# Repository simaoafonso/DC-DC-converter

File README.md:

# DC-DC-converter
CONVERSOR DC-DC ISOLADO PARA ENERGY ROUTER

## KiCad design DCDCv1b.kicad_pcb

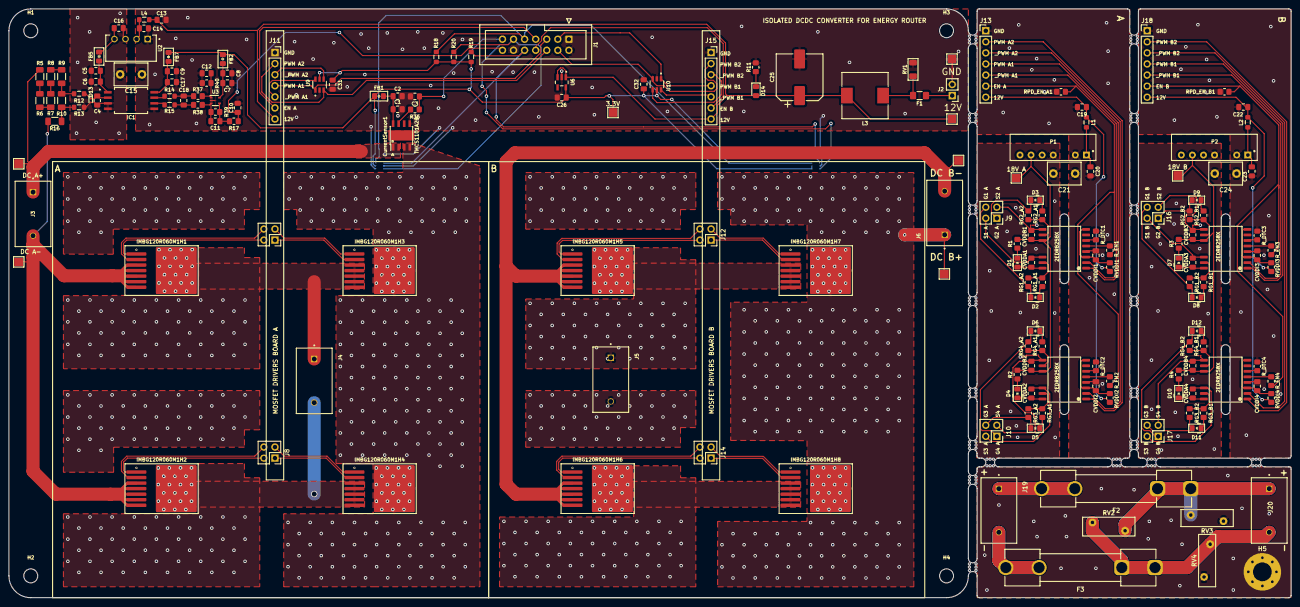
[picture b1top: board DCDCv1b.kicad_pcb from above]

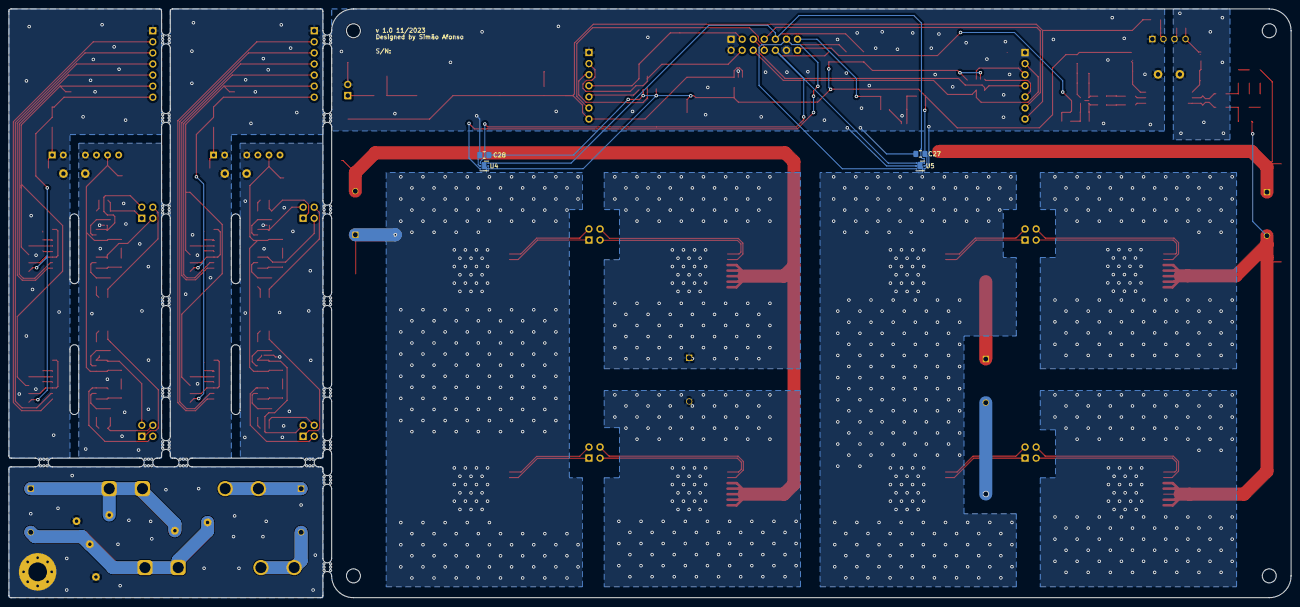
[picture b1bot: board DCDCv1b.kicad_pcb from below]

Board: 2 copper layers, 294.0 x 135.0 mm, 205 parts (4 on the bottom side), 112 nets.

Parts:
2EDR8258X1, 2EDR8258X2, 2EDR8258X3, 2EDR8258X4: U; 2EDR8258X
3.3V, 18V A, 18V B: TestPoint; TestPoint_Pad_2.0x2.0mm
C1, C7, C17: 4.7u; C_0805_2012Metric_Pad1.18x1.45mm_HandSolder
C2, C3, C6, C8, C9, C10, C18, C27, C28, C31, C32: 0.1u; C_0805_2012Metric_Pad1.18x1.45mm_HandSolder
C4: 0.01u; C_0805_2012Metric_Pad1.18x1.45mm_HandSolder
C5: 1u; C_0805_2012Metric_Pad1.18x1.45mm_HandSolder
C11, C12: 680p; C_0805_2012Metric_Pad1.18x1.45mm_HandSolder
C13, C14: 4.7u 50v; C_0805_2012Metric_Pad1.18x1.45mm_HandSolder
C15: 270p 2kV; C_Disc_D7.5mm_W5.0mm_P5.00mm
C16: 10u 16v; C_0805_2012Metric_Pad1.18x1.45mm_HandSolder
C19, C20, C22, C23: 2.2u 100v; C_0805_2012Metric_Pad1.18x1.45mm_HandSolder
C21, C24: 470p 2kV; C_Disc_D7.5mm_W5.0mm_P5.00mm
C25: 680u 25V; CP_Elec_10x14.3
C26: 2.2u; C_0805_2012Metric_Pad1.18x1.45mm_HandSolder
CVDDA1, CVDDA2, CVDDA3, CVDDA4: 0.1uF; C_0805_2012Metric_Pad1.18x1.45mm_HandSolder
CVDDB1, CVDDB2, CVDDB3, CVDDB4: 0.1uF; C_0805_2012Metric_Pad1.18x1.45mm_HandSolder
CVDDI1, CVDDI2, CVDDI3, CVDDI4: 10n; C_0805_2012Metric_Pad1.18x1.45mm_HandSolder
CurrentSensor1: TMCS1101A2B; SOIC-8-1EP_3.9x4.9mm_Pitch1.27mm_HandSolder
D1, D2, D3, D4, D5, D6, D7, D8, D9, D10, D11, D12: D; D_0805_2012Metric_Pad1.15x1.40mm_HandSolder
D13: ESD5B5.0ST1G; D_SOD-923
D14: LED; LED_0805_2012Metric_Pad1.15x1.40mm_HandSolder
DC A-: TestPoint; TestPoint_Pad_2.0x2.0mm
DC B-: TestPoint; TestPoint_Pad_2.0x2.0mm
F1: 1A; Fuse_1206_3216Metric_Pad1.42x1.75mm_HandSolder
F2, F3: Fuse; Fuseholder_Clip-6.3x32mm_Littelfuse_102_Inline_P34.21x7.62m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
FB1, FB2, FB5, FB7: MH2029-300Y; Ferrite_0805_2012Metric_Pad1.15x1.40mm_BigPads
H1, H2, H3, H4: MountingHole; MountingHole_3.2mm_M3
H5: MountingHole_Pad; MountingHole_4.3mm_M4_Pad_Via
IC1: AMC1311DWVR; SOIC127P1150X280-8N
IMBG120R060M1H1, IMBG120R060M1H2, IMBG120R060M1H3, IMBG120R060M1H4, IMBG120R060M1H5, IMBG120R060M1H6, IMBG120R060M1H7, IMBG120R060M1H8: TO-263-7_TabPin8
J1: Conn_02x07_Odd_Even; IDC-Header_2x07_P2.54mm_Vertical
J2: Conn_01x02_Pin; PinHeader_1x02_P2.54mm_Vertical
J3, J4, J5, J6, J19, J20: 282838-2; TE_282838-2
J7, J8, J12, J14: Conn_02x02_Counter_Clockwise; PinSocket_2x02_P2.54mm_Vertical
J9, J10, J16, J17: Conn_02x02_Counter_Clockwise; PinHeader_2x02_P2.54mm_Vertical
J11, J15: Conn_01x07_Socket; PinSocket_1x07_P2.54mm_Vertical
J13, J18: Conn_01x07_Pin; PinHeader_1x07_P2.54mm_Vertical
L1, L2: 18u; L_0805_2012Metric_Pad1.05x1.20mm_HandSolder
L3: 82u; L_10.4x10.4_H4.8
L4: 6.8u; L_0805_2012Metric_Pad1.05x1.20mm_HandSolder
NT1, NT2, NT3, NT4: NetTie_2; R_01005_0402Metric
P1, P2: AM2D-1218SZ; AM2D-NZ
R1, R2, R3, R4: 2.4; R_0805_2012Metric_Pad1.20x1.40mm_HandSolder
R5, R6, R7, R8, R9: 402k 250mW; R_1206_3216Metric_Pad1.30x1.75mm_HandSolder
R10: 4K53 250mW; R_1206_3216Metric_Pad1.30x1.75mm_HandSolder
R11: 510; R_0805_2012Metric_Pad1.20x1.40mm_HandSolder
R12, R13: 39; L_0805_2012Metric_Pad1.05x1.20mm_HandSolder
R14, R15: 1k; L_0805_2012Metric_Pad1.05x1.20mm_HandSolder
R16: 0.001 1W; R_1206_3216Metric_Pad1.30x1.75mm_HandSolder
R17, R36: 68.1; R_0805_2012Metric_Pad1.20x1.40mm_HandSolder
R18, R19, R20: 5k; L_0805_2012Metric_Pad1.05x1.20mm_HandSolder
R37, R38: 1k; R_0805_2012Metric_Pad1.20x1.40mm_HandSolder
R39, R40: 3k2; R_0805_2012Metric_Pad1.20x1.40mm_HandSolder
RG1_A1, RG1_A2, RG1_B1, RG1_B2, RG2_A1, RG2_A2, RG2_B1, RG2_B2, RG3_A1, RG3_A2, RG3_B1, RG3_B2, RG4_A1, RG4_A2, RG4_B1, RG4_B2: 2.4; R_0805_2012Metric_Pad1.20x1.40mm_HandSolder
RPD_EN_A1: 10k; R_0805_2012Metric_Pad1.20x1.40mm_HandSolder
RPD_EN_B1: 10k; R_0805_2012Metric_Pad1.20x1.40mm_HandSolder
RV1: 14V; R_1206_3216Metric_Pad1.30x1.75mm_HandSolder
RV2: Varistor; RV_Disc_D12mm_W4.3mm_P7.5mm
RV3, RV4: Varistor; RV_Disc_D12mm_W3.9mm_P7.5mm
RVDDI1, RVDDI2, RVDDI3, RVDDI4: 3k; R_0805_2012Metric_Pad1.20x1.40mm_HandSolder
R_DTC1, R_DTC2, R_DTC3, R_DTC4: 10k; R_0805_2012Metric_Pad1.20x1.40mm_HandSolder
R_EN1, R_EN2, R_EN3, R_EN4: 10k; R_0805_2012Metric_Pad1.20x1.40mm_HandSolder
TP5, TP9, TP11, TP33: TestPoint; TestPoint_Pad_2.0x2.0mm
U2: PQS075-S12-S5-S; CONV_PQS075-S12-S5-S
U3: TLV6001DCK; SOT-353_SC-70-5
U4, U5: TMP117xxDRV; WSON-6-1EP_2x2mm_P0.65mm_EP1x1.6mm
U6: MIC5225-3.3YM5-TR; SOT95P280X145-5N
U9, U10: SN74LVC2G14DBVR; SOT95P280X145-6N
mouse-bite-2mm-slot, mouse-bite-2mm-slot#2, mouse-bite-2mm-slot#3, mouse-bite-2mm-slot#4, mouse-bite-2mm-slot#5, mouse-bite-2mm-slot#6, mouse-bite-2mm-slot#7, mouse-bite-2mm-slot#8, mouse-bite-2mm-slot#9, mouse-bite-2mm-slot#10, mouse-bite-2mm-slot#11, mouse-bite-2mm-slot#12, mouse-bite-2mm-slot#13, mouse-bite-2mm-slot#14, mouse-bite-2mm-slot#15, mouse-bite-2mm-slot#16, mouse-bite-2mm-slot#17, mouse-bite-2mm-slot#18: VAL**; mouse-bite-2mm-slot

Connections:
+12V: F1.1, J2.1
/3.3V: 3.3V.1, C26.1, C27.1, C28.1, C31.1, C32.1, FB1.1, FB2.1, FB7.1, R18.1, R19.1, R20.1, U4.4 (ADD0), U4.5 (V+), U5.5 (V+), U6.5 (OUT), U9.5 (VCC), U10.5 (VCC)
/5V_A: C16.1, FB5.2, U2.4 (+VO)
/12V: C13.1, C19.1, C22.1, C25.1, D14.2 (A), J11.7, J13.7, J15.7, J18.7, L1.1, L2.1, L3.2, L4.1, RVDDI1.1, RVDDI2.1, RVDDI3.1, RVDDI4.1, TP9.1, U6.1 (IN), U6.3 (EN)
/18V_A: 2EDR8258X1.11 (VDDB), 2EDR8258X2.11 (VDDB), 18V A.1, CVDDB1.1, CVDDB2.1, P1.5 (VOUT), R1.2, R2.2
/18V_B: 2EDR8258X3.11 (VDDB), 2EDR8258X4.11 (VDDB), 18V B.1, CVDDB3.1, CVDDB4.1, P2.5 (VOUT), R3.2, R4.2
/DC+: F2.2, J19.1
/DC-: F3.2, J19.2
/DC_A: CurrentSensor1.3 (IN-), CurrentSensor1.4 (IN-), IMBG120R060M1H3.8 (Drain), IMBG120R060M1H4.8 (Drain)
/DC_B: IMBG120R060M1H7.8 (Drain), IMBG120R060M1H8.8 (Drain), J6.1, TP33.1
/DC_M_A: CurrentSensor1.1 (IN+), CurrentSensor1.2 (IN+), J3.1, R5.2, TP5.1
/DC_OUT+: F2.1, J20.1, RV2.1, RV3.1
/DC_OUT-: F3.1, J20.2, RV2.2, RV4.1
/EN_A: J1.7, J11.6, J13.6, RPD_EN_A1.1, R_EN1.1, R_EN2.1
/EN_B: J1.8, J15.6, J18.6, RPD_EN_B1.1, R_EN3.1, R_EN4.1
/G1_A: D2.2 (A), IMBG120R060M1H3.1 (Gate), J7.2, J9.4, RG1_A2.2
/G1_B: D8.2 (A), IMBG120R060M1H7.1 (Gate), J12.2, J16.4, RG1_B2.2
/G2_A: D3.2 (A), IMBG120R060M1H1.1 (Gate), J7.3, J9.1, RG2_A2.2
/G2_B: D9.2 (A), IMBG120R060M1H5.1 (Gate), J12.3, J16.1, RG2_B2.2
/G3_A: D5.2 (A), IMBG120R060M1H4.1 (Gate), J8.2, J10.4, RG3_A2.2
/G3_B: D11.2 (A), IMBG120R060M1H8.1 (Gate), J14.2, J17.4, RG3_B2.2
/G4_A: D6.2 (A), IMBG120R060M1H2.1 (Gate), J8.3, J10.1, RG4_A2.2
/G4_B: D12.2 (A), IMBG120R060M1H6.1 (Gate), J14.3, J17.1, RG4_B2.2
/HP: J1.11, R20.2, U4.3 (ALERT), U5.3 (ALERT)
/I_M_A: C3.1, J1.13, R36.1
/PWM_A1: 2EDR8258X1.1 (INA), J1.5, J11.4, J13.4, U9.1 (1A)
/PWM_A2: 2EDR8258X2.1 (INA), J1.6, J11.2, J13.2, U9.3 (2A)
/PWM_B1: 2EDR8258X3.1 (INA), J1.3, J15.4, J18.4, U10.1 (1A)
/PWM_B2: 2EDR8258X4.1 (INA), J1.4, J15.2, J18.2, U10.3 (2A)
/S1_A: 2EDR8258X1.12 (GNDA), CVDDA1.2, IMBG120R060M1H3.2 (Sense), J7.1, J9.2
/S1_B: 2EDR8258X3.12 (GNDA), CVDDA3.2, IMBG120R060M1H7.2 (Sense), J12.1, J16.2
/S2_A: 2EDR8258X1.9 (GNDB), CVDDB1.2, IMBG120R060M1H1.2 (Sense), J7.4, J9.3, NT1.2
/S2_B: 2EDR8258X3.9 (GNDB), CVDDB3.2, IMBG120R060M1H5.2 (Sense), J12.4, J16.3, NT4.2
/S3_A: 2EDR8258X2.12 (GNDA), CVDDA2.2, IMBG120R060M1H4.2 (Sense), J8.1, J10.2
/S3_B: 2EDR8258X4.12 (GNDA), CVDDA4.2, IMBG120R060M1H8.2 (Sense), J14.1, J17.2
/S4_A: 2EDR8258X2.9 (GNDB), CVDDB2.2, IMBG120R060M1H2.2 (Sense), J8.4, J10.3, NT2.2
/S4_B: 2EDR8258X4.9 (GNDB), CVDDB4.2, IMBG120R060M1H6.2 (Sense), J14.4, J17.3, NT3.2
/SCL: J1.10, R19.2, U4.1 (SCL), U5.1 (SCL)
/SDA: J1.9, R18.2, U4.6 (SDA), U5.6 (SDA)
/TransNP: IMBG120R060M1H2.8 (Drain), IMBG120R060M1H4.3 (Source), IMBG120R060M1H4.4 (Source), IMBG120R060M1H4.5 (Source), IMBG120R060M1H4.6 (Source), IMBG120R060M1H4.7 (Source), J4.2
/TransNS: IMBG120R060M1H6.8 (Drain), IMBG120R060M1H8.3 (Source), IMBG120R060M1H8.4 (Source), IMBG120R060M1H8.5 (Source), IMBG120R060M1H8.6 (Source), IMBG120R060M1H8.7 (Source), J5.2
/TransPP: IMBG120R060M1H1.8 (Drain), IMBG120R060M1H3.3 (Source), IMBG120R060M1H3.4 (Source), IMBG120R060M1H3.5 (Source), IMBG120R060M1H3.6 (Source), IMBG120R060M1H3.7 (Source), J4.1
/TransPS: IMBG120R060M1H5.8 (Drain), IMBG120R060M1H7.3 (Source), IMBG120R060M1H7.4 (Source), IMBG120R060M1H7.5 (Source), IMBG120R060M1H7.6 (Source), IMBG120R060M1H7.7 (Source), J5.1
/V_M_A: C10.2, J1.14, R17.2
//PWM_A1: 2EDR8258X1.2 (INB), J11.5, J13.5, U9.6 (1Y)
//PWM_A2: 2EDR8258X2.2 (INB), J11.3, J13.3, U9.4 (2Y)
//PWM_B1: 2EDR8258X3.2 (INB), J15.5, J18.5, U10.6 (1Y)
//PWM_B2: 2EDR8258X4.2 (INB), J15.3, J18.3, U10.4 (2Y)
Earth: H5.1, RV3.2, RV4.2
GND: 2EDR8258X1.4 (GNDI), 2EDR8258X2.4 (GNDI), 2EDR8258X3.4 (GNDI), 2EDR8258X4.4 (GNDI), C1.2, C2.2, C3.2, C7.2, C8.2, C9.1, C10.1, C12.2, C13.2, C14.2, C15.1, C17.1, C19.2, C20.2, C21.1, C22.2, C23.2, C24.1, C25.2, C26.2, C27.2, C28.2, C31.2, C32.2, CVDDI1.2, CVDDI2.2, CVDDI3.2, CVDDI4.2, CurrentSensor1.5 (GND), IC1.5 (GND2), J1.1, J1.2, J1.12, J2.2, J11.1, J13.1, J15.1, J18.1, P1.2 (GND), P2.2 (GND), R11.2, R40.1, RPD_EN_A1.2, RPD_EN_B1.2, RV1.2, R_DTC1.2, R_DTC2.2, R_DTC3.2, R_DTC4.2, TP11.1, U2.1 (GND), U3.2 (V-), U4.2 (GND), U5.2 (GND), U5.4 (ADD0), U6.2 (GND), U9.2 (GND), U10.2 (GND)
GND1: C4.2, C5.1, C6.1, C15.2, C16.2, C21.2, D13.2 (A2), DC A-.1, IC1.3 (SHTDN), IC1.4 (GND1), IMBG120R060M1H1.3 (Source), IMBG120R060M1H1.4 (Source), IMBG120R060M1H1.5 (Source), IMBG120R060M1H1.6 (Source), IMBG120R060M1H1.7 (Source), IMBG120R060M1H2.3 (Source), IMBG120R060M1H2.4 (Source), IMBG120R060M1H2.5 (Source), IMBG120R060M1H2.6 (Source), IMBG120R060M1H2.7 (Source), J3.2, NT1.1, NT2.1, P1.3 (GOUT), R13.1, R16.1, U2.3 (0V)
GND2: C24.2, DC B-.1, IMBG120R060M1H5.3 (Source), IMBG120R060M1H5.4 (Source), IMBG120R060M1H5.5 (Source), IMBG120R060M1H5.6 (Source), IMBG120R060M1H5.7 (Source), IMBG120R060M1H6.3 (Source), IMBG120R060M1H6.4 (Source), IMBG120R060M1H6.5 (Source), IMBG120R060M1H6.6 (Source), IMBG120R060M1H6.7 (Source), J6.2, NT3.1, NT4.1, P2.3 (GOUT)
unnamed: 2EDR8258X1.5 (DIS), R_EN1.2
unnamed: 2EDR8258X1.13 (OUTA), RG1_A1.1, RG1_A2.1
unnamed: 2EDR8258X1.10 (OUTB), RG2_A1.1, RG2_A2.1
unnamed: 2EDR8258X1.6 (STP/DTC), R_DTC1.1
unnamed: 2EDR8258X1.14 (VDDA), CVDDA1.1, D1.1 (K)
unnamed: 2EDR8258X1.3 (VDDI), 2EDR8258X1.8 (VDDI), CVDDI1.1, RVDDI1.2
unnamed: 2EDR8258X2.5 (DIS), R_EN2.2
unnamed: 2EDR8258X2.13 (OUTA), RG3_A1.1, RG3_A2.1
unnamed: 2EDR8258X2.10 (OUTB), RG4_A1.1, RG4_A2.1
unnamed: 2EDR8258X2.6 (STP/DTC), R_DTC2.1
unnamed: 2EDR8258X2.14 (VDDA), CVDDA2.1, D4.1 (K)
unnamed: 2EDR8258X2.3 (VDDI), 2EDR8258X2.8 (VDDI), CVDDI2.1, RVDDI2.2
unnamed: 2EDR8258X3.5 (DIS), R_EN3.2
unnamed: 2EDR8258X3.13 (OUTA), RG1_B1.1, RG1_B2.1
unnamed: 2EDR8258X3.10 (OUTB), RG2_B1.1, RG2_B2.1
unnamed: 2EDR8258X3.6 (STP/DTC), R_DTC3.1
unnamed: 2EDR8258X3.14 (VDDA), CVDDA3.1, D7.1 (K)
unnamed: 2EDR8258X3.3 (VDDI), 2EDR8258X3.8 (VDDI), CVDDI3.1, RVDDI3.2
unnamed: 2EDR8258X4.5 (DIS), R_EN4.2
unnamed: 2EDR8258X4.13 (OUTA), RG3_B1.1, RG3_B2.1
unnamed: 2EDR8258X4.10 (OUTB), RG4_B1.1, RG4_B2.1
unnamed: 2EDR8258X4.6 (STP/DTC), R_DTC4.1
unnamed: 2EDR8258X4.14 (VDDA), CVDDA4.1, D10.1 (K)
unnamed: 2EDR8258X4.3 (VDDI), 2EDR8258X4.8 (VDDI), CVDDI4.1, RVDDI4.2
unnamed: C11.1, R17.1, R39.1, U3.4
unnamed: C18.1, R14.1, R37.1
unnamed: C18.2, R15.1, R38.1
unnamed: CurrentSensor1.7 (VOUT), R36.2
unnamed: C1.1, C2.1, CurrentSensor1.8 (VS), FB1.2
unnamed: D1.2 (A), R1.1
unnamed: D2.1 (K), RG1_A1.2
unnamed: D3.1 (K), RG2_A1.2
unnamed: D4.2 (A), R2.1
unnamed: D5.1 (K), RG3_A1.2
unnamed: D6.1 (K), RG4_A1.2
unnamed: D7.2 (A), R3.1
unnamed: D8.1 (K), RG1_B1.2
unnamed: D9.1 (K), RG2_B1.2
unnamed: D10.2 (A), R4.1
unnamed: D11.1 (K), RG3_B1.2
unnamed: D12.1 (K), RG4_B1.2
unnamed: C4.1, D13.1 (A1), IC1.2 (VIN), R12.1
unnamed: D14.1 (K), R11.1
unnamed: F1.2, L3.1, RV1.1
unnamed: C5.2, C6.2, FB5.1, IC1.1 (VDD1)
unnamed: C9.2, C17.2, FB7.2, IC1.8 (VDD2)
unnamed: IC1.6 (VOUTN), R15.2
unnamed: IC1.7 (VOUTP), R14.2
unnamed: C20.1, L1.2, P1.1 (VCC)
unnamed: C23.1, L2.2, P2.1 (VCC)
unnamed: R5.1, R6.2
unnamed: R6.1, R7.2
unnamed: R7.1, R8.2
unnamed: R8.1, R9.2
unnamed: R10.1, R13.2, R16.2
unnamed: R9.1, R10.2, R12.2
unnamed: C14.1, L4.2, U2.2 (VIN)
unnamed: C12.1, R37.2, R40.2, U3.1 (+)
unnamed: C11.2, R38.2, R39.2, U3.3 (-)
unnamed: C7.1, C8.1, FB2.2, U3.5 (V+)
